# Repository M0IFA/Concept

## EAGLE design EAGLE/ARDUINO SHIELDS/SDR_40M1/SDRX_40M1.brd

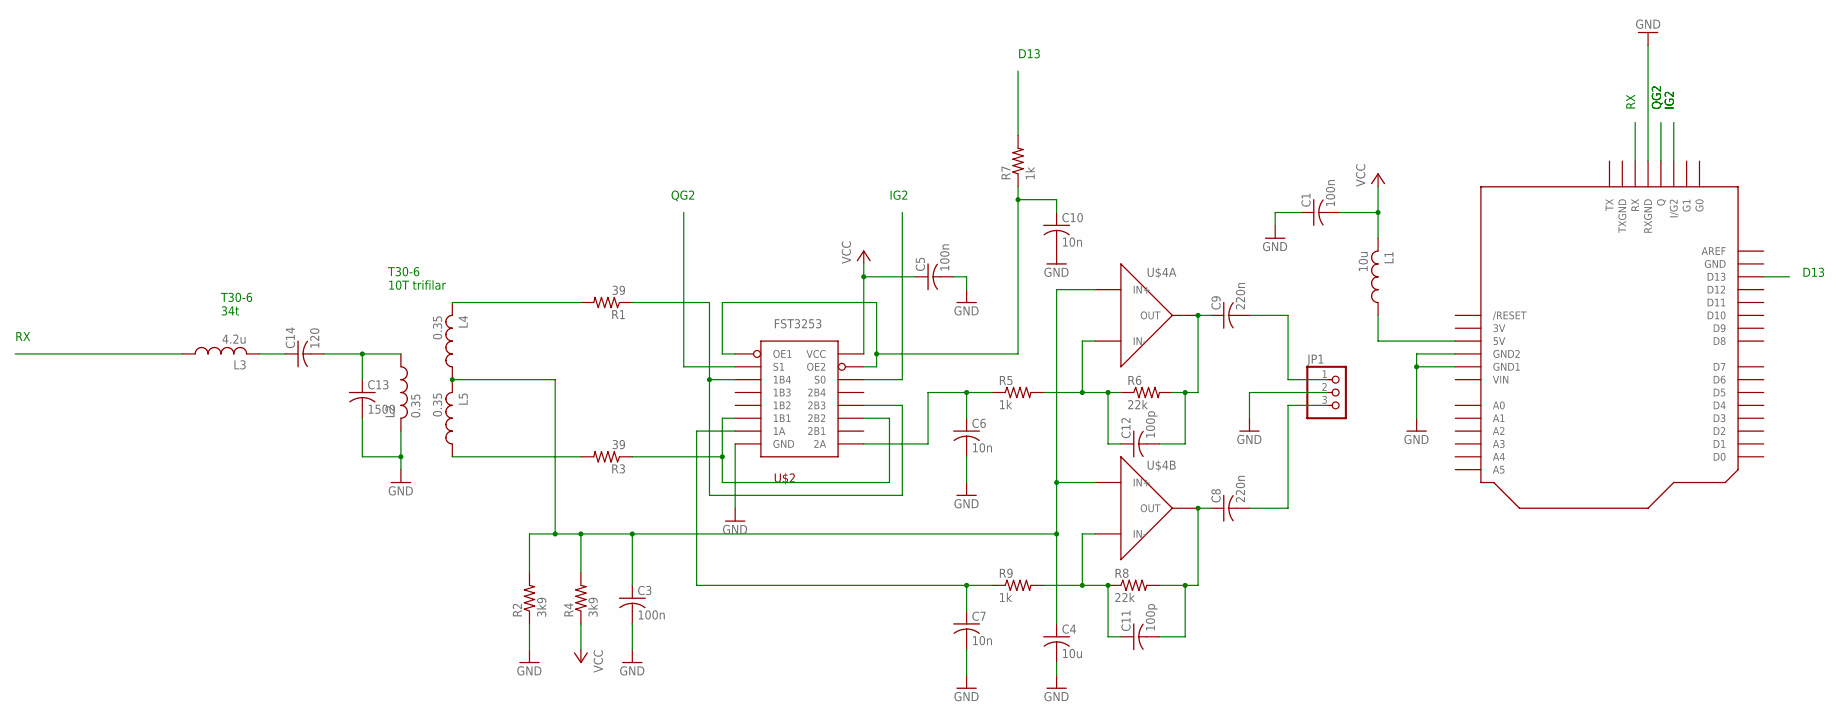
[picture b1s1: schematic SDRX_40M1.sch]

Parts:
C1, C3, C5: 100n; C050-030X075
C4: 10u; C050-030X075
C6, C7, C10: 10n; C050-030X075
C8, C9: 220n; C050-030X075
C11, C12: 100p; C050-030X075
C13: 1500; C050-025X075
C14: 120; C050-025X075
JP1: PINHD-1X3; 1X03
L1: 10u; 0207/10
L2, L4, L5: 0.35; 0207/10
L3: 4.2u; 0207/10
R1, R3: 39; 0207/10
R2, R4: 3k9; 0207/10
R5, R7, R9: 1k; 0207/10
R6, R8: 22k; 0207/10
U$1: RF-SHIELD; SHIELD-RF
U$2: FST3253
U$4: TLV2462

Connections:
3V: U$1.3V
D13: R7.2, U$1.D13
GND: C1.1, C3.2, C4.2, C5.2, C6.2, C7.2, C10.2, C13.2, JP1.2, L2.2, R2.1, U$1.GND, U$1.GND1, U$1.GND2, U$1.RXGND, U$2.GND, U$4.4 (GND)
IG2: U$1.I/G2, U$2.S0
unnamed: C3.1, C4.1, L4.1, L5.2, R2.2, R4.2, U$4.3 (IN+), U$4.5 (IN+)
unnamed: C13.1, C14.2, L2.1
unnamed: L4.2, R1.2
unnamed: L1.1, U$1.5V
unnamed: R3.1, U$2.1B1, U$2.2B2
unnamed: L5.1, R3.2
unnamed: R1.1, U$2.1B4, U$2.2B3
unnamed: C14.1, L3.2
unnamed: C10.1, R7.1, U$2.OE1, U$2.OE2
unnamed: C9.1, C12.2, R6.2, U$4.1 (OUT)
unnamed: C9.2, JP1.1
unnamed: C8.1, C11.2, R8.2, U$4.7 (OUT)
unnamed: C8.2, JP1.3
unnamed: C11.1, R8.1, R9.2, U$4.6 (IN-)
unnamed: C12.1, R5.2, R6.1, U$4.2 (IN-)
unnamed: C7.1, R9.1, U$2.1A
unnamed: C6.1, R5.1, U$2.2A
QG2: U$1.Q, U$2.S1
RX: L3.1, U$1.RX
TXGND: U$1.TXGND
VCC: C1.2, C5.1, L1.2, R4.1, U$2.VCC, U$4.8 (VCC)
VIN: U$1.VIN

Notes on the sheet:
D13
QG2
IG2
T30-6 34t
T30-6 10T trifilar

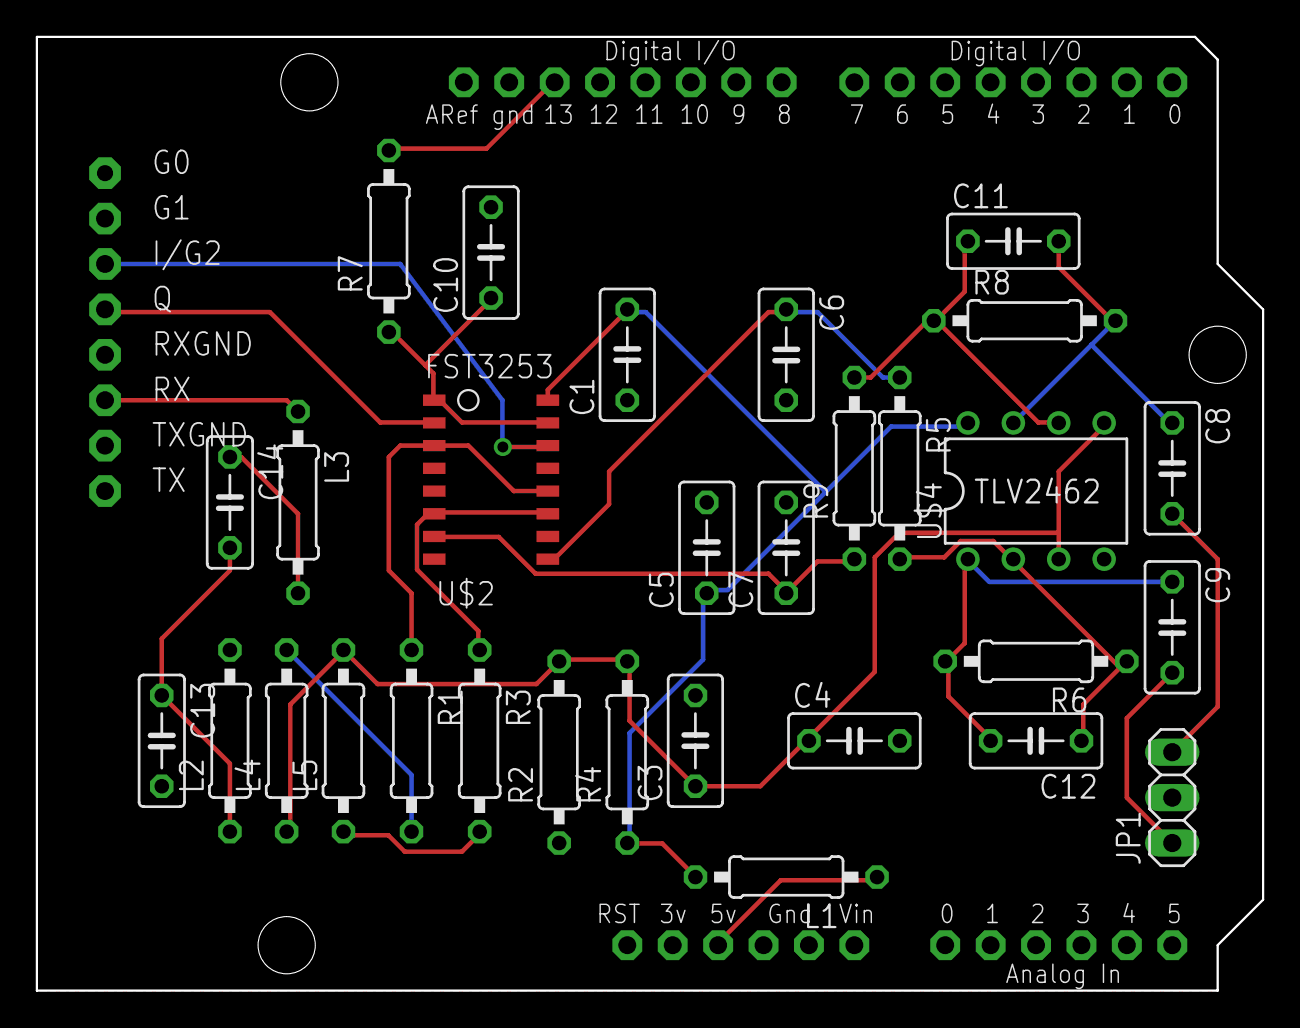
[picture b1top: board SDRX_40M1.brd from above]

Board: 2 copper layers, 68.6 x 53.3 mm, 31 parts (0 on the bottom side), 23 nets.

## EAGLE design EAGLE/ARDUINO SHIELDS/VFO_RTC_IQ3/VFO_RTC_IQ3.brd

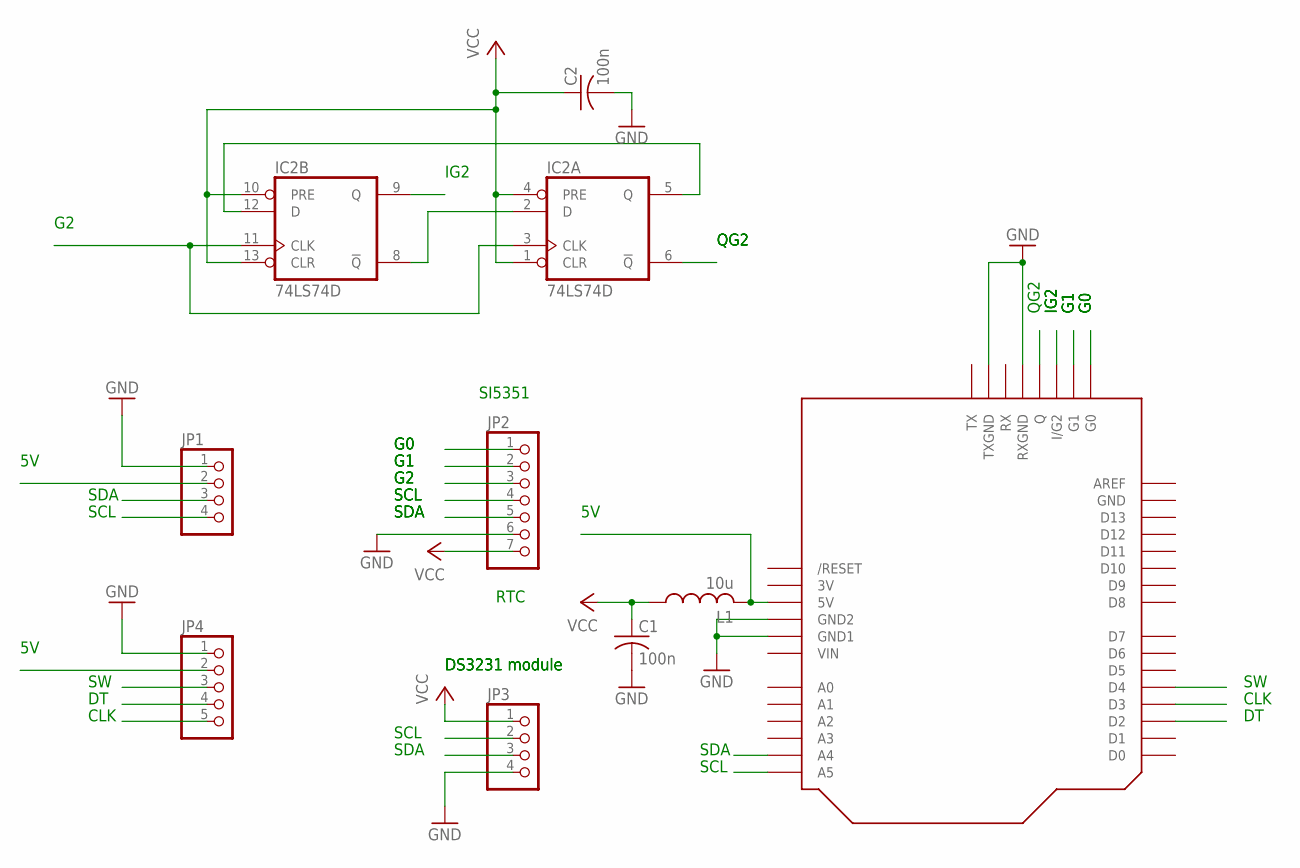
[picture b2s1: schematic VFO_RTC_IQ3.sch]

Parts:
C1, C2: 100n; C050-025X075
IC2: 74LS74D; SO14
JP1, JP3: PINHD-1X4; 1X04
JP2: PINHD-1X7; 1X07
JP4: PINHD-1X5; 1X05
L1: 10u; 0207/10
U$1: RF-SHIELD; SHIELD-RF

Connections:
3V: U$1.3V
5V: JP1.2, JP4.2, L1.2, U$1.5V
CLK: JP4.5, U$1.D3
DT: JP4.4, U$1.D2
G0: JP2.1, U$1.G0
G1: JP2.2, U$1.G1
G2: IC2.3 (CLK), IC2.11 (CLK), JP2.3
GND: C1.2, C2.2, IC2.7 (GND), JP1.1, JP2.6, JP3.4, JP4.1, U$1.GND, U$1.GND1, U$1.GND2, U$1.RXGND, U$1.TXGND
IG2: IC2.9 (Q), U$1.I/G2
unnamed: IC2.2 (D), IC2.8 (!Q)
unnamed: IC2.5 (Q), IC2.12 (D)
QG2: IC2.6 (!Q), U$1.Q
SCL: JP1.4, JP2.4, JP3.2, U$1.A5
SDA: JP1.3, JP2.5, JP3.3, U$1.A4
SW: JP4.3, U$1.D4
VCC: C1.1, C2.1, IC2.1 (CLR), IC2.4 (PRE), IC2.10 (PRE), IC2.13 (CLR), IC2.14 (VCC), JP2.7, JP3.1, L1.1
VIN: U$1.VIN

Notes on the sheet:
SCL
SDA
SI5351
RTC
CLK
IG2
QG2
DS3231 module

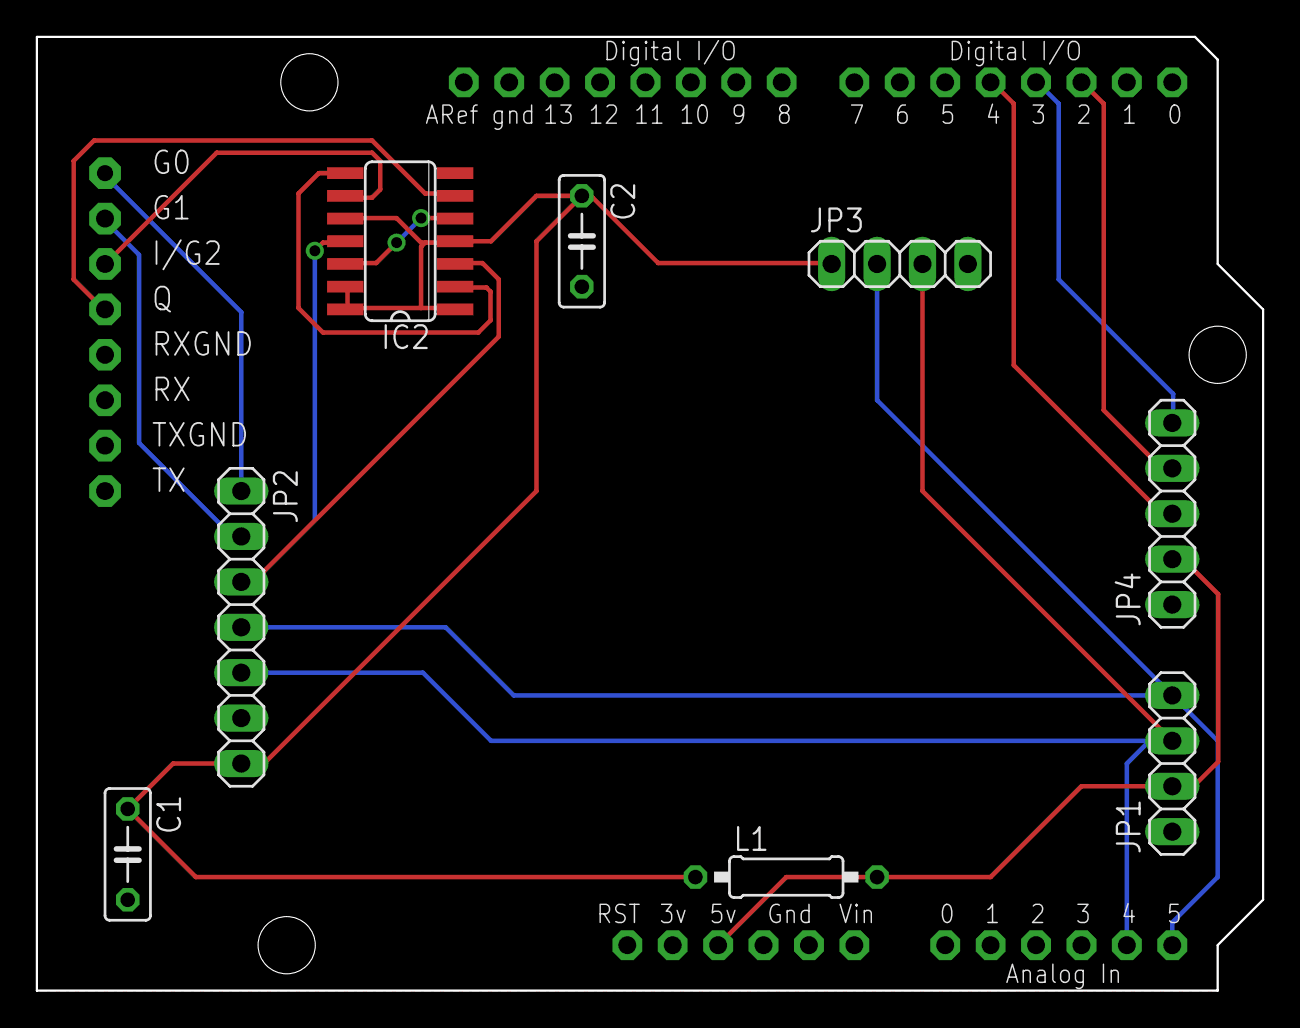
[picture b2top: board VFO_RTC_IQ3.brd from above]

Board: 2 copper layers, 68.6 x 53.3 mm, 9 parts (0 on the bottom side), 15 nets.

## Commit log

2015-10-13 Release 1.0
    Full Concept course and software
2015-10-13 Duplicate file
    File/slide updated
